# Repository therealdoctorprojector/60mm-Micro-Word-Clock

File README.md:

# 60mm Micro Word Clock

Based on:

https://github.com/formatc1702/Micro-Word-Clock

Licence:

http://creativecommons.org/licenses/by-sa/3.0/

What has not been changed:

* The firmware. This uses the same version of the firmware as per Rojas' project. I've tested the English language firmware.
* The hardware. The clock still uses the ATmega microcontroller with a DS1307Z RTC to keep time.

What has been changed:

* I have moved the pins to correctly drive a 60mm LED display (the 2088BS, 16 pin type).
* Added a PCB mount battery holder for the RTC.
* Added a USB socket for the power supply.

The BOM is almost the same as the original project, with the following changes:

* Add PCB mount micro USB socket
* Add PCB mount CR2032 battery holder
* Delete 20mm display
* Add 60mm display

You need the circuit board as described in the Eagle files attached. Or you can order it from here if you do not want to make any changes:

https://oshpark.com/shared_projects/ba7Lkx4g

The display I'm using is marked "KYX-2088BS", but it seems the "2088BS" part is the most important.
The columns are commoned to cathodes and the rows are commoned to anodes.

The battery holder is a PCB mount holder for a CR2032 cell.
The USB socket is "USB_MICRO-B_SMT" from the SparkFun Connectors library:

https://www.sparkfun.com/products/retired/8533

If you're making your own board, you can change the connector before sending _your_ PCB to your chosen manufacturer.

26/2/2021

Ready-to-roll word mask PCB here:

https://oshpark.com/shared_projects/uc8ES2uw

Not required, as there are other methods to make this part.

8/6/2021

Alternative word mask PCB, with the copper on the uppermost layer:

https://oshpark.com/shared_projects/ZUiYG7Su

14/6/2021

Added the .brd files for the word masks, if you feel the need to make any changes to them.

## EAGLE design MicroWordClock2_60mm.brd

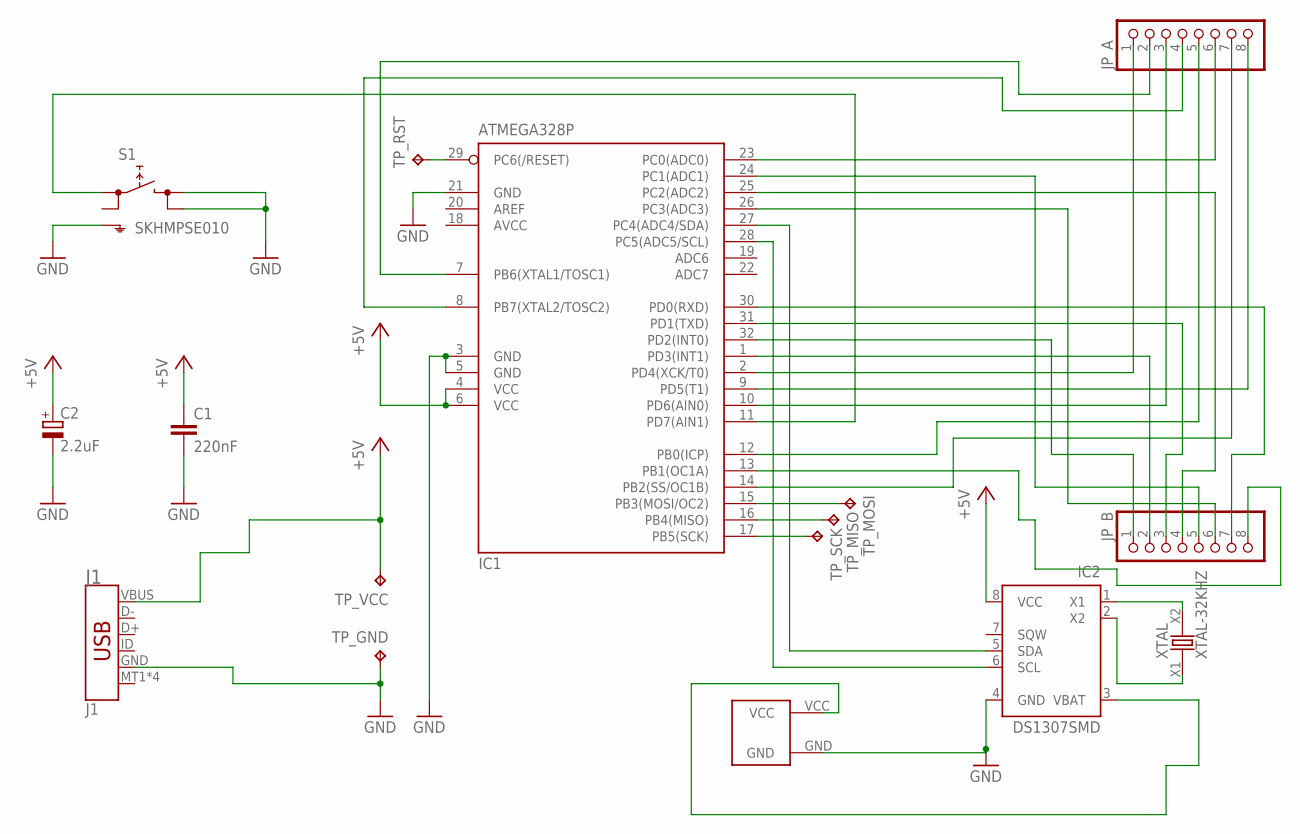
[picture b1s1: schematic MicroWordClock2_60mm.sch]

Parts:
C1: 220nF; C0805
C2: 2.2uF; B/3528-21R
IC1: ATMEGA328P; TQFP32-08
IC2: DS1307SMD; SO-08M
J1: J1; USB-MICROB
JP_A: PINHD-1X8CLEANBIG; 1X08-CLEANBIG
JP_B: PINHD-1X8CLEANBIG; 1X08-CLEANBIG
S1: SKHMPSE010; SKHMPXE010
TP_GND: TPB1,27; B1,27
TP_MISO: TPB1,27; B1,27
TP_MOSI: TPB1,27; B1,27
TP_RST: TPB1,27; B1,27
TP_SCK: TPB1,27; B1,27
TP_VCC: TPB1,27; B1,27
U$1: CR2032; CR2032-20MM
XTAL: XTAL-32KHZ; XTAL-SMD-1206-3216M

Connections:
+5V: C1.1, C2.+, IC1.4 (VCC), IC1.6 (VCC), IC2.8 (VCC), J1.VBUS, TP_VCC.TP
A7: IC1.10 (PD6(AIN0)), JP_A.3
A8: IC1.8 (PB7(XTAL2/TOSC2)), JP_A.4
AVCC: IC1.18 (AVCC)
B8: IC1.7 (PB6(XTAL1/TOSC1)), JP_A.2
GND: C1.2, C2.-, IC1.3 (GND), IC1.5 (GND), IC1.21 (GND), IC2.4 (GND), J1.GND, S1.3 (2.1), S1.4 (2.2), S1.5 (SH), TP_GND.TP, U$1.GND
MISO: IC1.16 (PB4(MISO)), TP_MISO.TP
MOSI: IC1.15 (PB3(MOSI/OC2)), TP_MOSI.TP
unnamed: IC1.12 (PB0(ICP)), JP_A.5
unnamed: IC2.2 (X2), XTAL.X1
unnamed: IC1.2 (PD4(XCK/T0)), JP_A.1
unnamed: IC1.23 (PC0(ADC0)), JP_A.6
unnamed: IC1.14 (PB2(SS/OC1B)), JP_A.7
unnamed: IC1.9 (PD5(T1)), JP_A.8
unnamed: IC1.32 (PD2(INT0)), JP_B.1
unnamed: IC1.1 (PD3(INT1)), JP_B.2
unnamed: IC1.31 (PD1(TXD)), JP_B.3
unnamed: IC1.25 (PC2(ADC2)), JP_B.4
unnamed: IC2.3 (VBAT), U$1.VCC
unnamed: IC1.24 (PC1(ADC1)), JP_B.5
unnamed: IC1.26 (PC3(ADC3)), JP_B.6
unnamed: IC2.1 (X1), XTAL.X2
unnamed: IC1.30 (PD0(RXD)), JP_B.7
unnamed: IC1.13 (PB1(OC1A)), JP_B.8
unnamed: IC1.28 (PC5(ADC5/SCL)), IC2.6 (SCL)
RESET: IC1.29 (PC6(/RESET)), TP_RST.TP
SCK: IC1.17 (PB5(SCK)), TP_SCK.TP
SDA: IC1.27 (PC4(ADC4/SDA)), IC2.5 (SDA)
SWITCH: IC1.11 (PD7(AIN1)), S1.1 (1.1)

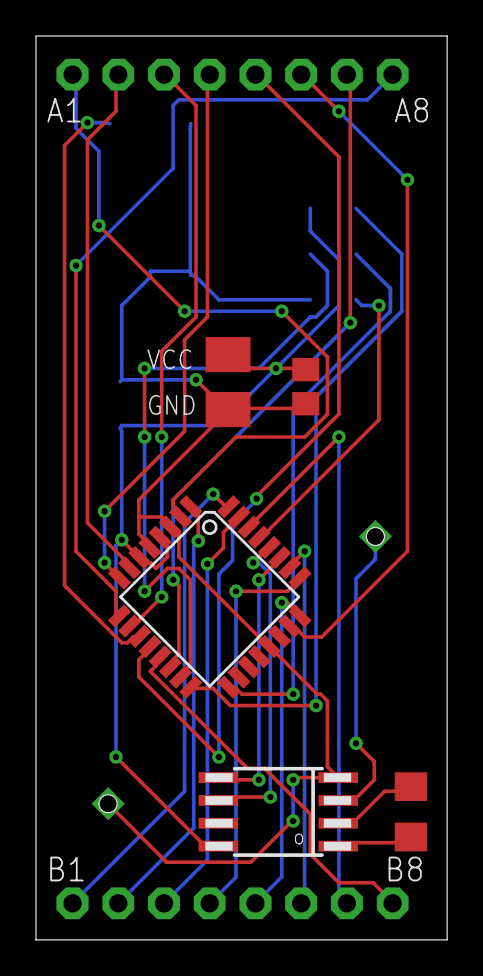
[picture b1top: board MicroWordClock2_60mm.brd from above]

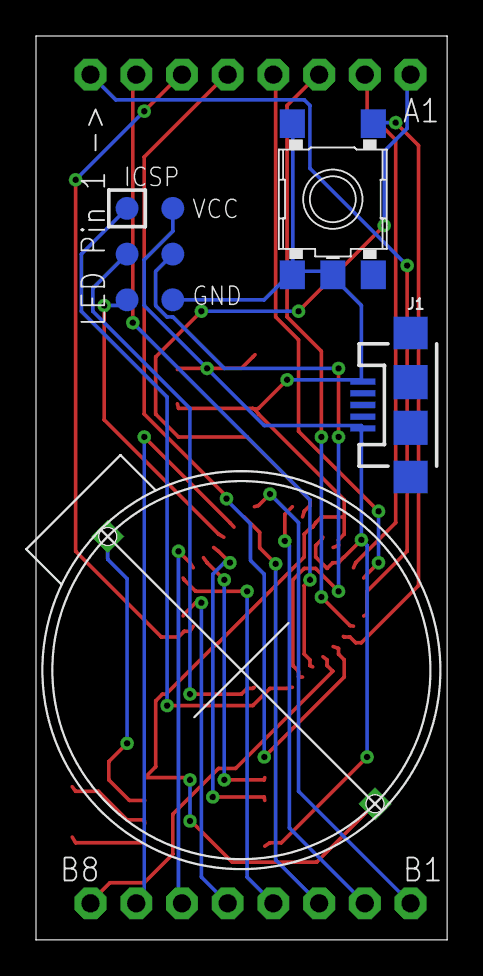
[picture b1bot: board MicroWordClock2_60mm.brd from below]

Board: 2 copper layers, 22.8 x 50.2 mm, 16 parts (9 on the bottom side), 28 nets.

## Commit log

2021-06-14 Add files via upload
    Word mask PCB with the copper layer mirrored so the letters are invisible when not lit.
2021-06-14 Add files via upload
    PCB Word mask with the copper on the top. The letters will be visible regardless of if they are lit or not.

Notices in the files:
parts and their libraries:
SparkFun-Connectors: Licensing: Creative Commons ShareAlike 4.0 International - https://creativecommons.org/licenses/by-sa/4.0
